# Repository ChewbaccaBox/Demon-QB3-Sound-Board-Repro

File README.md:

# Demon-QB3-Sound-Board

***UNTESTED AND POSSIBLY INCOMPLETE***\
Gerbers not included because of this.

Here is my reproduction sound board of those
used in Rockola's Demon and QB3, both based
on Cinematronics hardware. 
So, these games are both impossible to find,
and therefore the sound boards are too.
Demon uses practically a standard Cinematronics
CPU board, and QB3 is a bit more complicated
to make hardware for, but this sound board
should work for the two games.
(QB3 has more ram, a color converter PCB, the sound roms
 dumped are broken. But Demon should work with less trouble!)

**TESTING STATUS:**

no clue! gotta double check the schematic based on the original.
This is being built on solely the two schematics (the QB3 one 
looks more accurate/complete, so leaning towards that one)

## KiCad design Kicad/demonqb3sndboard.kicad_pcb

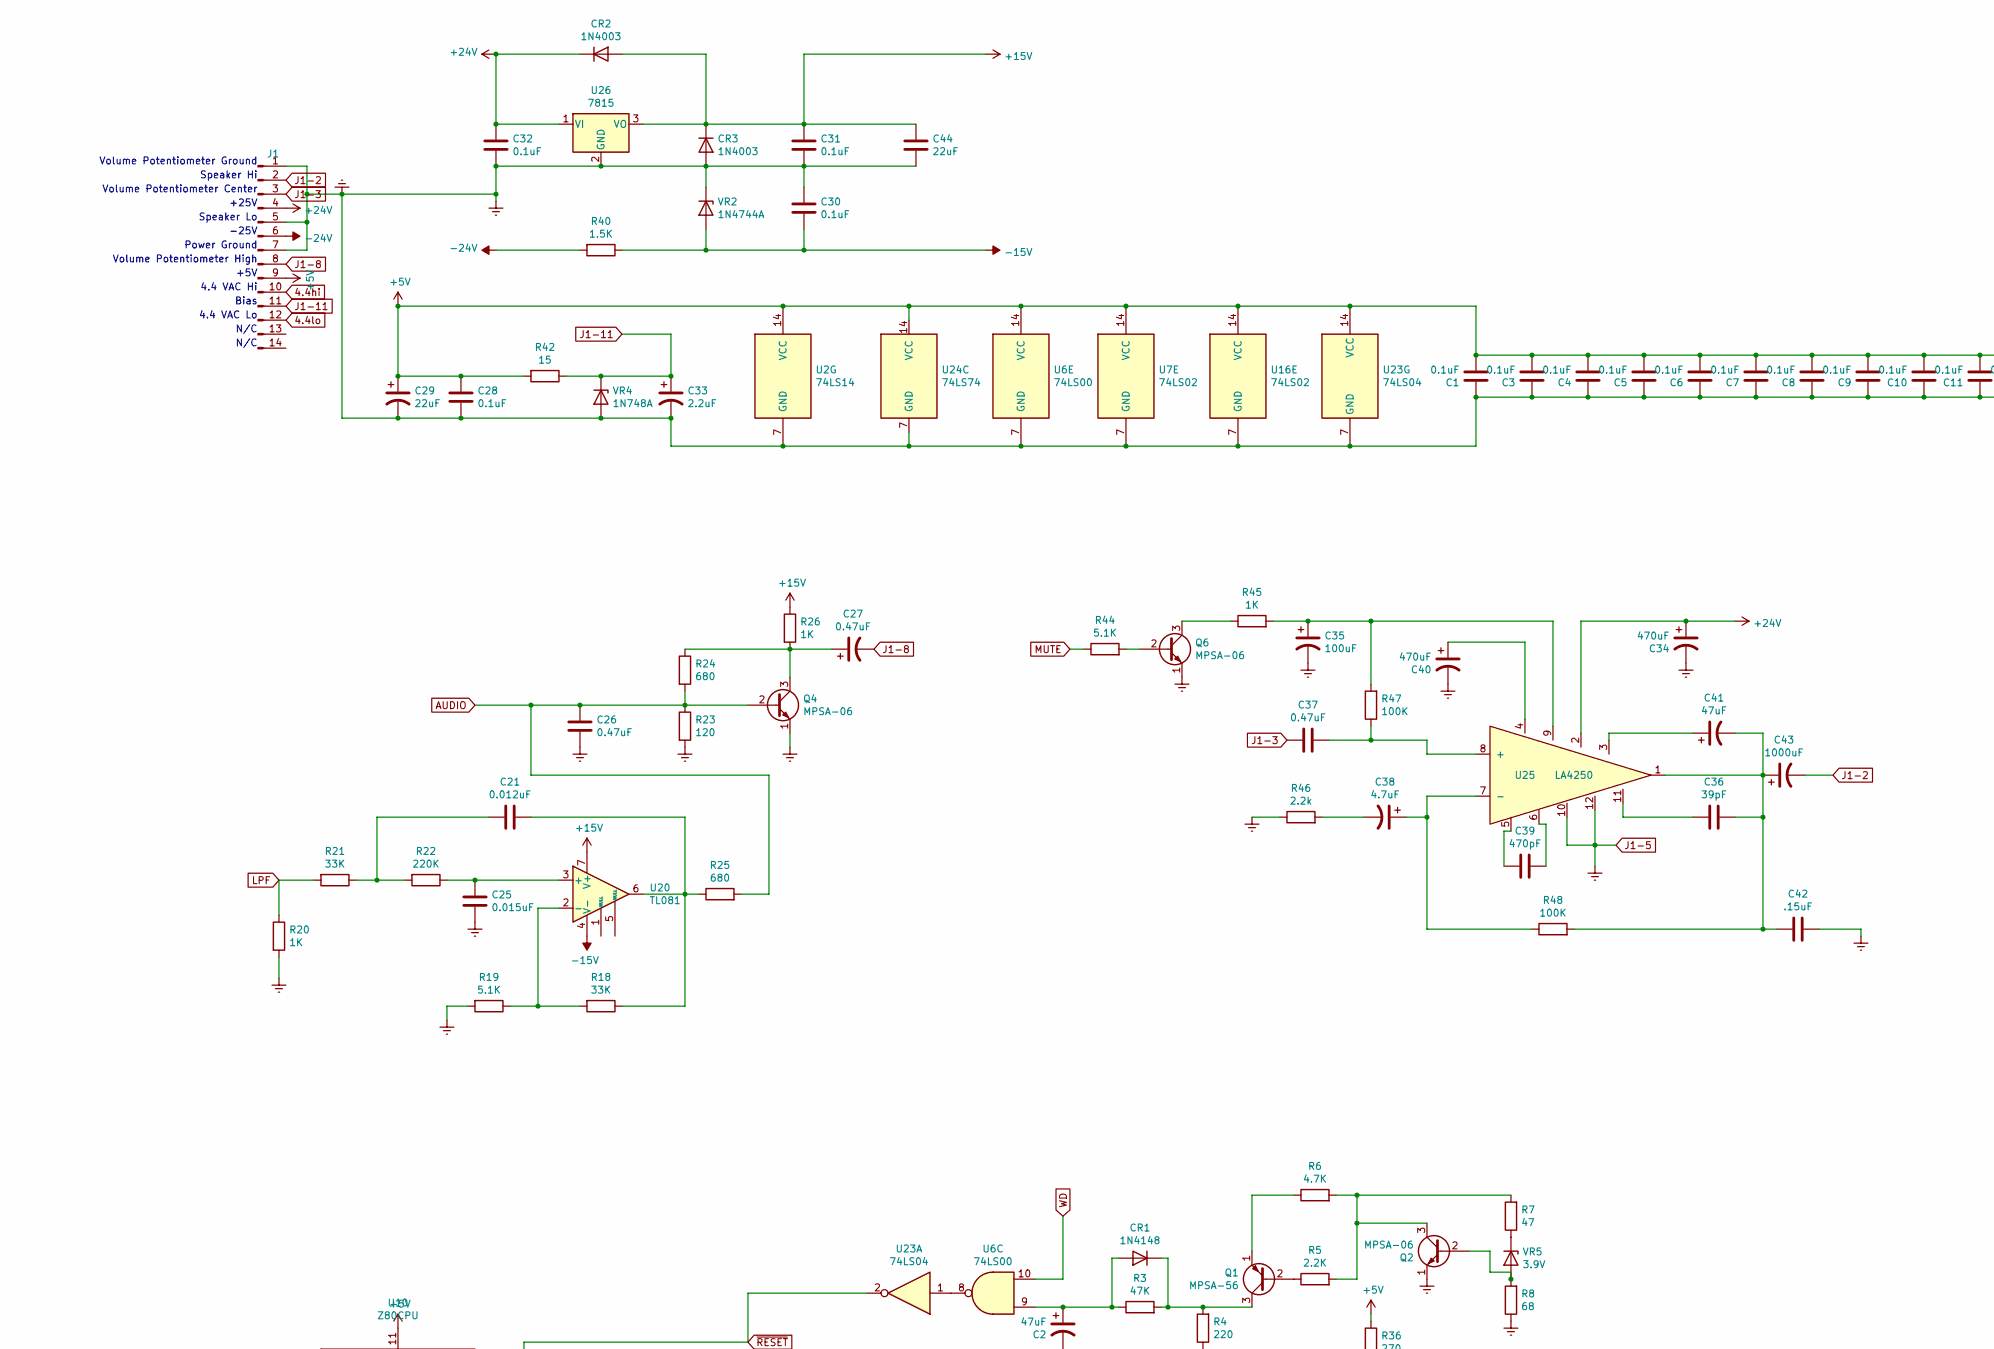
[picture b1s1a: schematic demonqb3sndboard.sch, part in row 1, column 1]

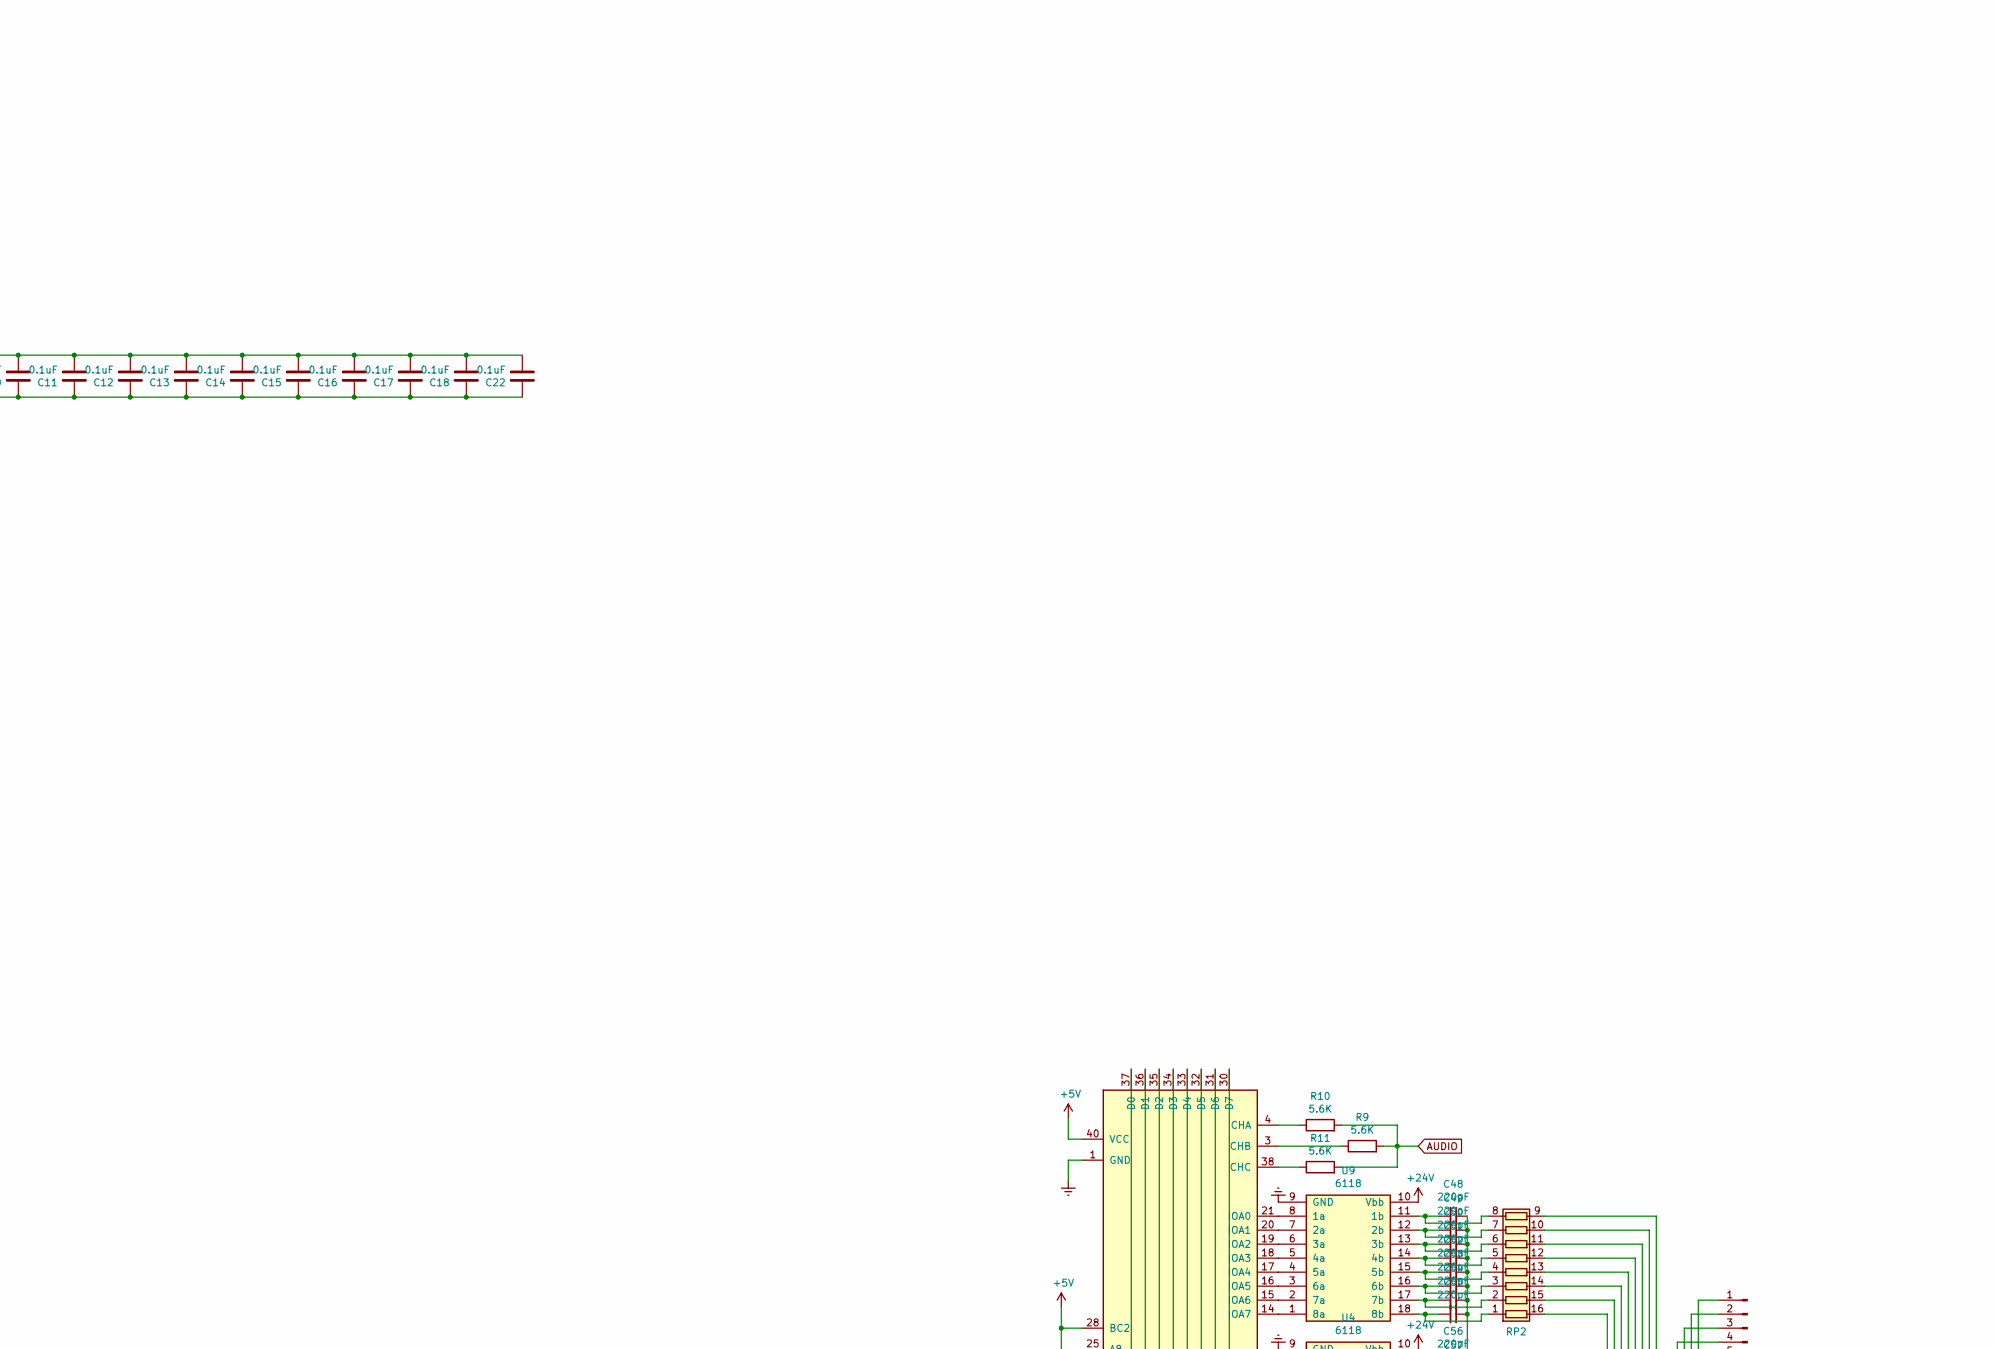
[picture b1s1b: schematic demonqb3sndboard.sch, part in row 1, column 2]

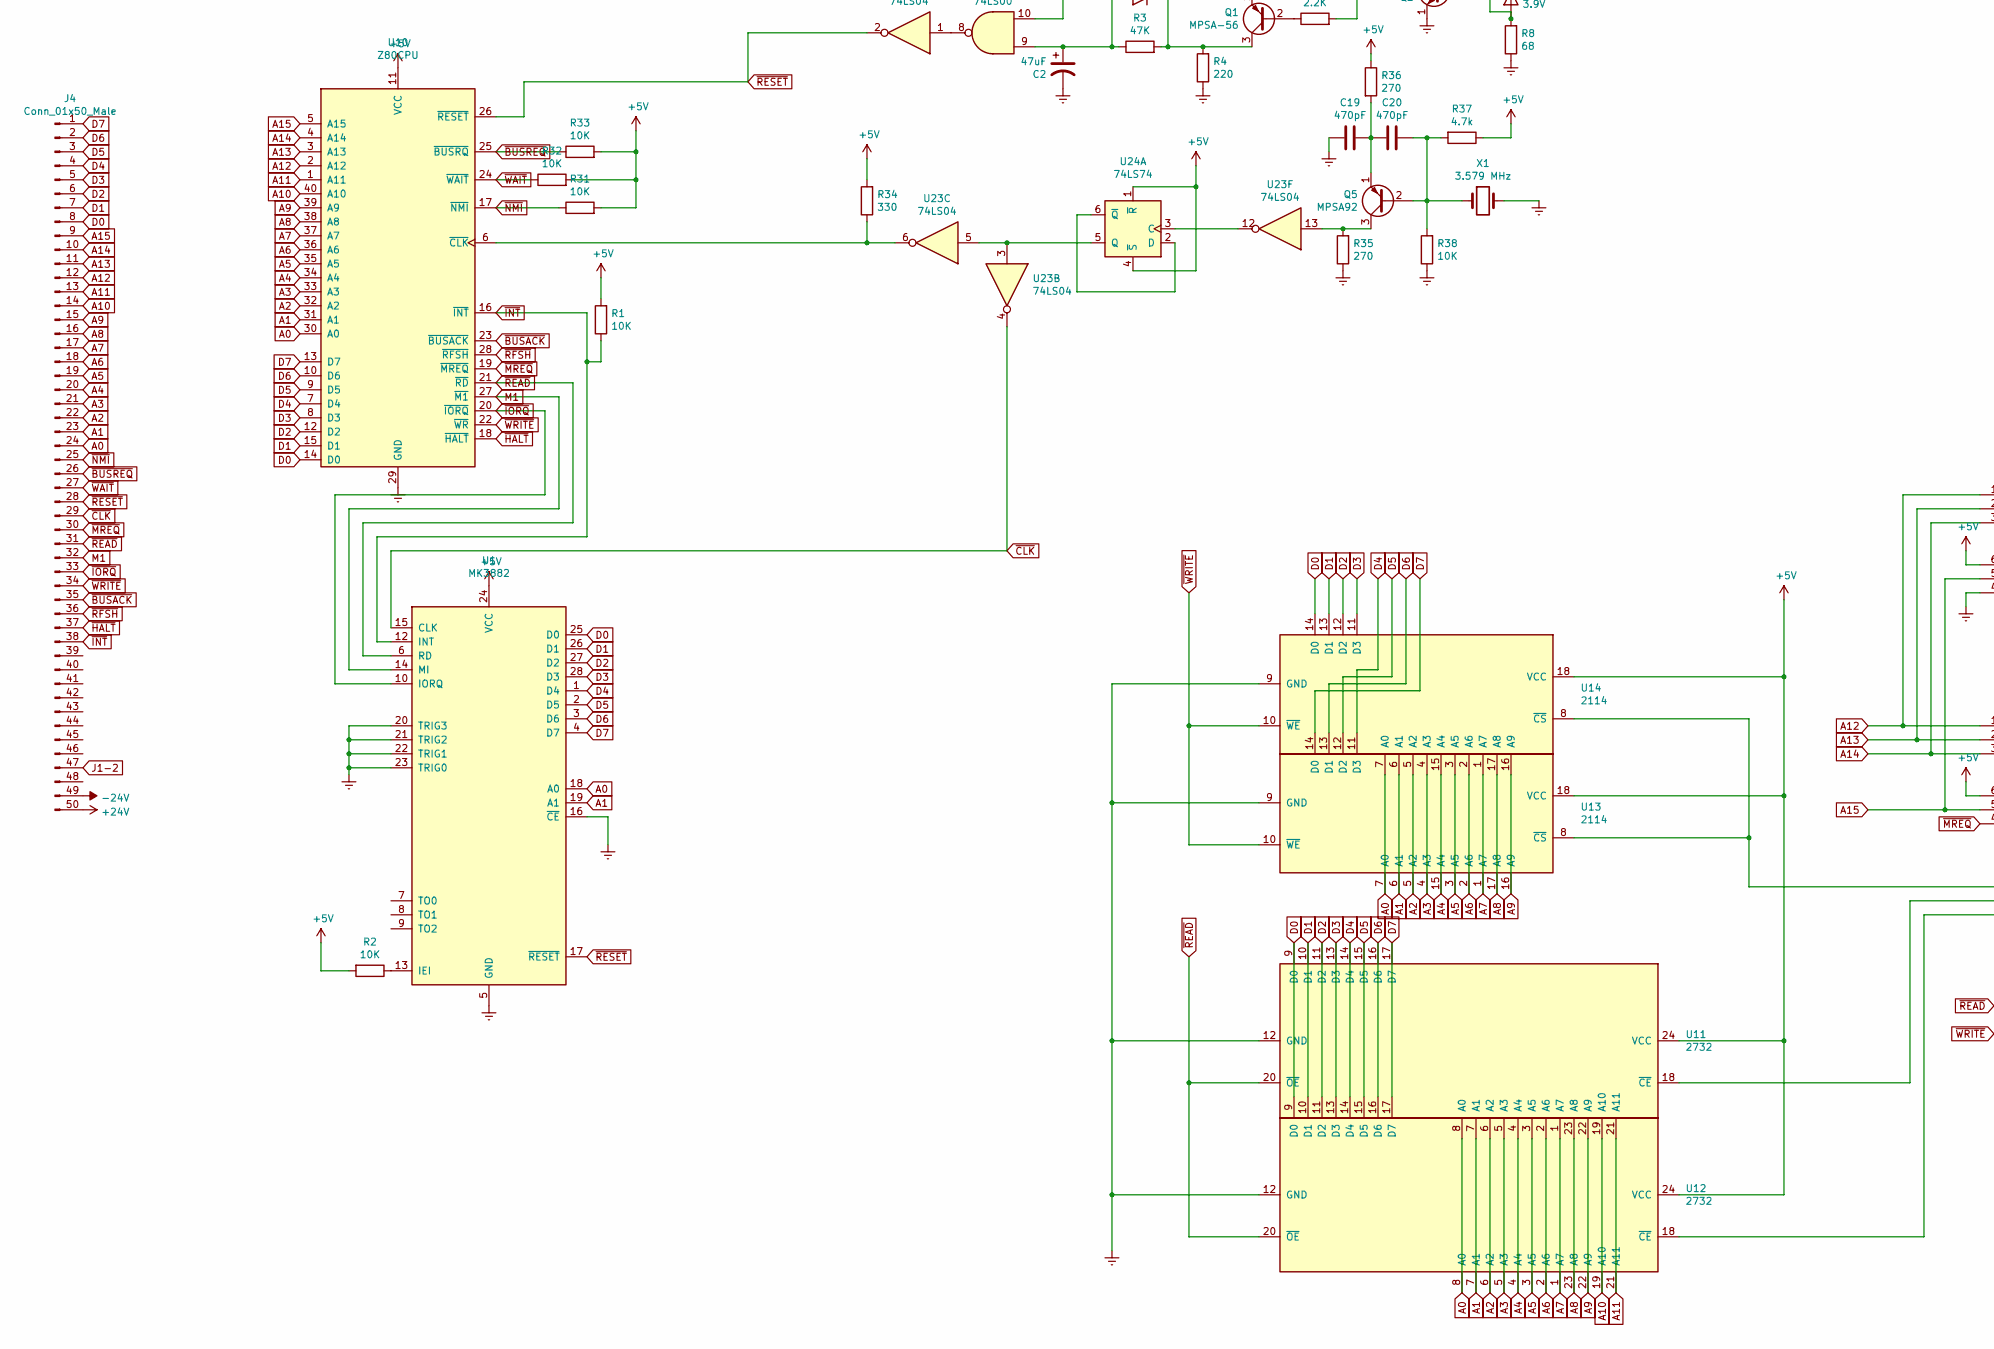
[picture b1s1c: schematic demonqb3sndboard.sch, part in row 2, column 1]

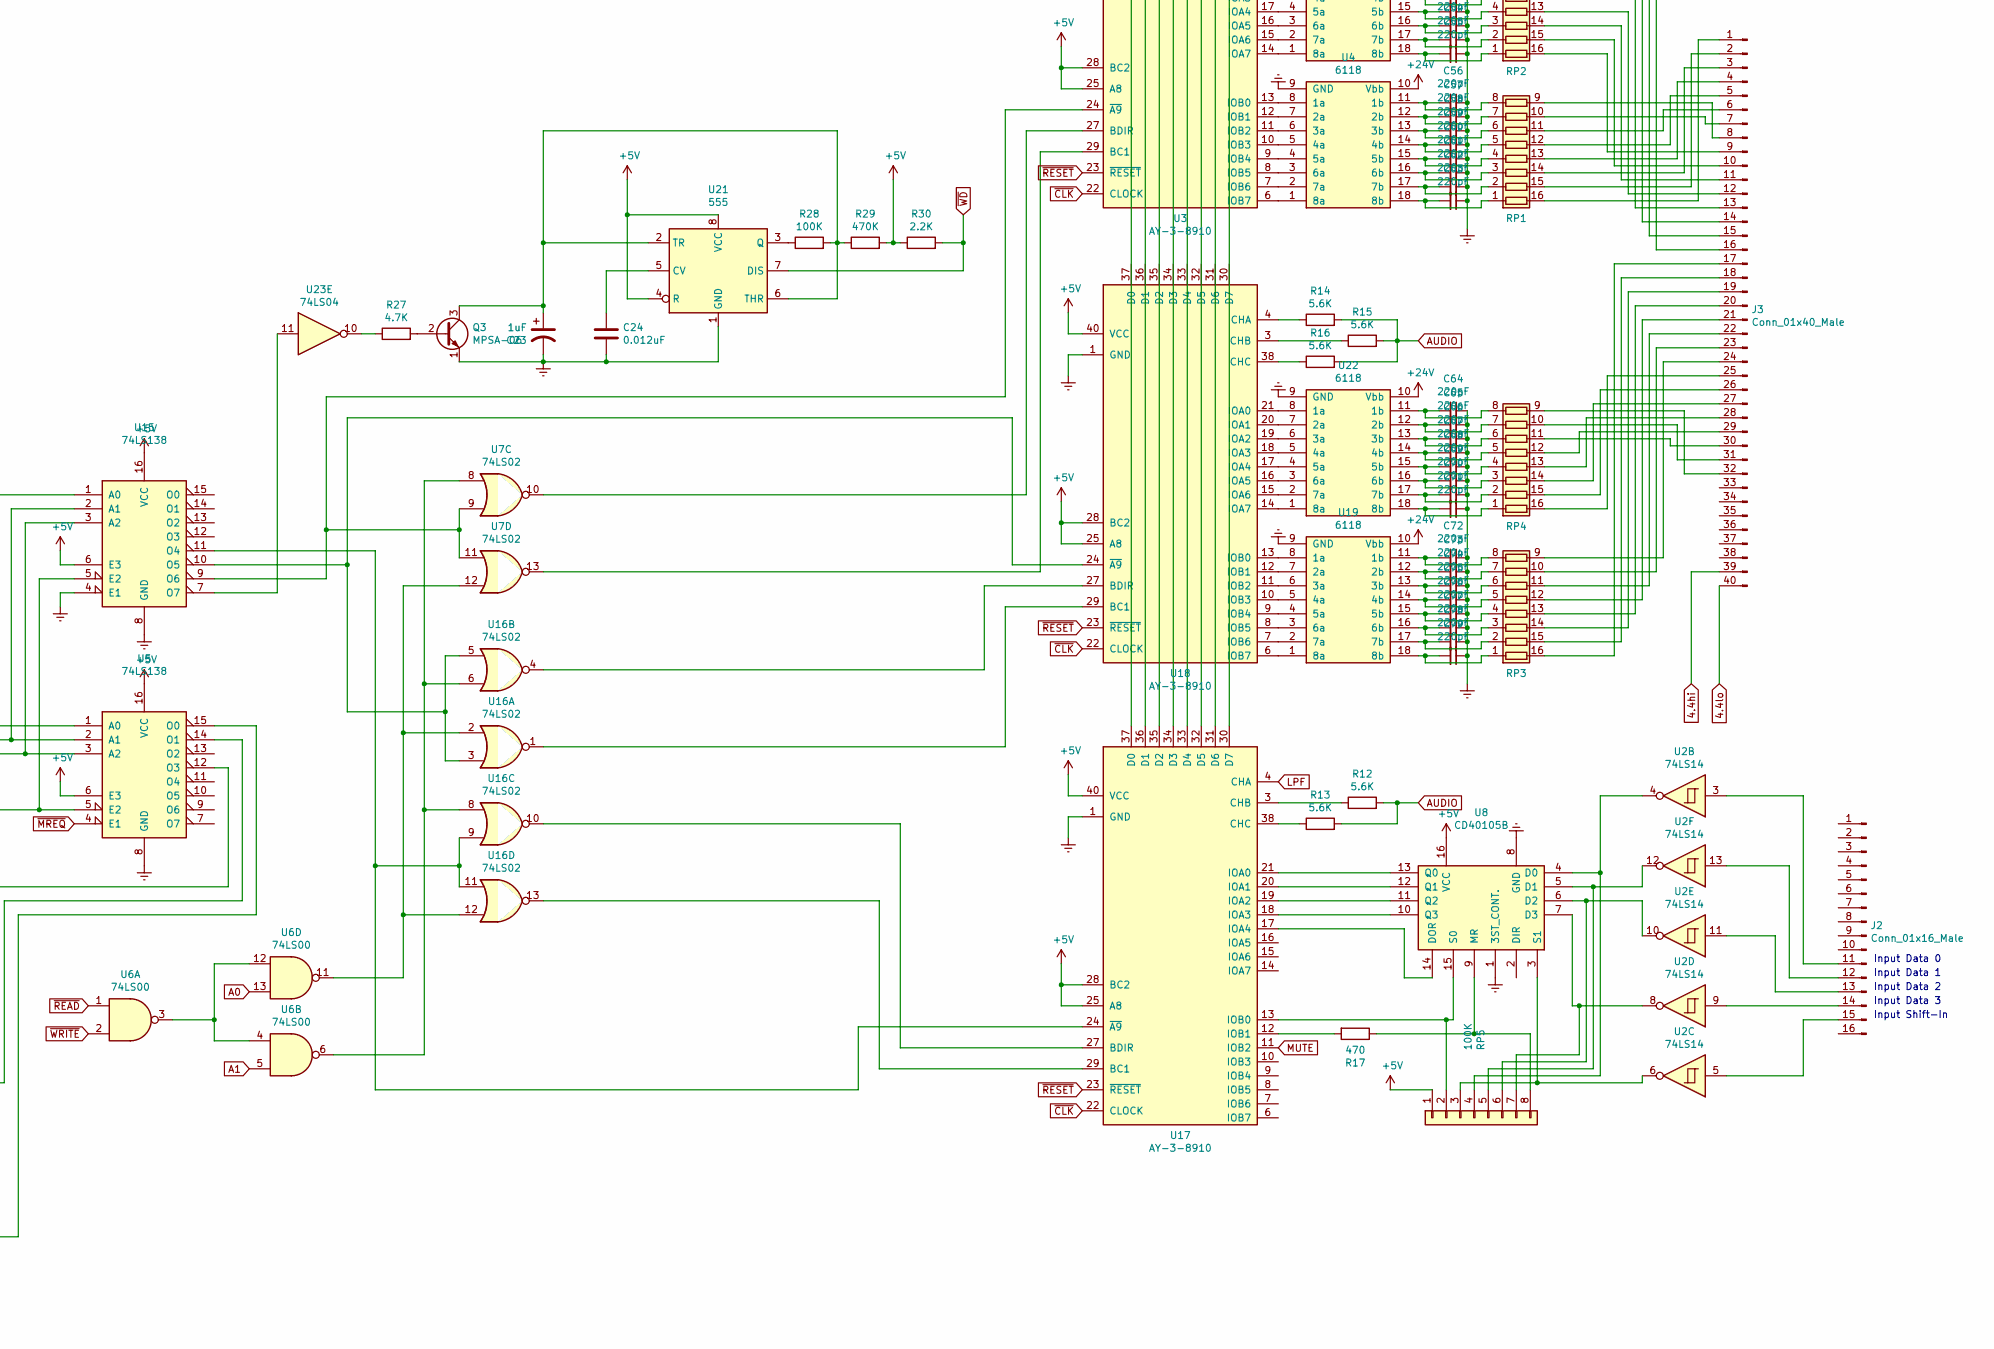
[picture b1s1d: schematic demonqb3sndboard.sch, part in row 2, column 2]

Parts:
C1, C3, C4, C5, C6, C7, C8, C9, C10, C11, C12, C13, C14, C15, C16, C17, C18, C22, C28, C30, C31, C32: 0.1uF; C_Disc_D7.0mm_W2.5mm_P5.00mm
C2: 47uF; CP_Radial_D10.0mm_P5.00mm
C19, C20, C39: 470pF; C_Disc_D7.0mm_W2.5mm_P5.00mm
C21, C24: 0.012uF; C_Disc_D12.5mm_W5.0mm_P10.00mm
C23: 1uF; C_Disc_D10.0mm_W2.5mm_P5.00mm
C25: 0.015uF; C_Disc_D12.5mm_W5.0mm_P10.00mm
C26, C27: 0.47uF; C_Disc_D7.0mm_W2.5mm_P5.00mm
C29, C44: 22uF; C_Disc_D7.0mm_W2.5mm_P5.00mm
C33: 2.2uF; C_Disc_D7.0mm_W2.5mm_P5.00mm
C34, C40: 470uF; CP_Radial_D10.0mm_P5.00mm
C35: 100uF; CP_Radial_D5.0mm_P2.50mm
C36: 39pF; C_Disc_D7.0mm_W2.5mm_P5.00mm
C37: 0.47uF; CP_Radial_D5.0mm_P2.50mm
C38: 4.7uF; C_Disc_D7.0mm_W2.5mm_P5.00mm
C41: 47uF; CP_Radial_D5.0mm_P2.50mm
C42: .15uF; C_Disc_D7.0mm_W2.5mm_P5.00mm
C43: 1000uF; CP_Axial_L30.0mm_D10.0mm_P35.00mm_Horizontal
C48, C49, C50, C51, C52, C53, C54, C55, C56, C57, C58, C59, C60, C61, C62, C63, C64, C65, C66, C67, C68, C69, C70, C71, C72, C73, C74, C75, C76, C77, C78, C79: 220pF; C_Disc_D7.0mm_W2.5mm_P5.00mm
CR1: 1N4148; D_DO-41_SOD81_P10.16mm_Horizontal
CR2, CR3: 1N4003; D_DO-41_SOD81_P10.16mm_Horizontal
J1: Conn_01x14_Male; PinHeader_01x14_0.156
J2: Conn_01x16_Male; PinHeader_2x08_P2.54mm_Vertical
J3: Conn_01x40_Male; 40pinEdgeConnector2.54mm
J4: Conn_01x50_Male; 50pinEdgeConnector2.54mm
Q1: MPSA-56; TO-92_Inline
Q2, Q3, Q4, Q6: MPSA-06; TO-92_Inline
Q5: MPSA92; TO-92_Inline
R1, R2, R31, R32, R33, R38: 10K; R_Axial_DIN0309_L9.0mm_D3.2mm_P12.70mm_Horizontal
R3: 47K; R_Axial_DIN0309_L9.0mm_D3.2mm_P12.70mm_Horizontal
R4: 220; R_Axial_DIN0309_L9.0mm_D3.2mm_P12.70mm_Horizontal
R5, R30: 2.2K; R_Axial_DIN0309_L9.0mm_D3.2mm_P12.70mm_Horizontal
R6, R27: 4.7K; R_Axial_DIN0309_L9.0mm_D3.2mm_P12.70mm_Horizontal
R7: 47; R_Axial_DIN0309_L9.0mm_D3.2mm_P12.70mm_Horizontal
R8: 68; R_Axial_DIN0309_L9.0mm_D3.2mm_P12.70mm_Horizontal
R9, R10, R11, R12, R13, R14, R15, R16: 5.6K; R_Axial_DIN0309_L9.0mm_D3.2mm_P12.70mm_Horizontal
R17: 470; R_Axial_DIN0309_L9.0mm_D3.2mm_P12.70mm_Horizontal
R18, R21: 33K; R_Axial_DIN0309_L9.0mm_D3.2mm_P12.70mm_Horizontal
R19, R44: 5.1K; R_Axial_DIN0309_L9.0mm_D3.2mm_P12.70mm_Horizontal
R20, R26, R45: 1K; R_Axial_DIN0309_L9.0mm_D3.2mm_P12.70mm_Horizontal
R22: 220K; R_Axial_DIN0309_L9.0mm_D3.2mm_P12.70mm_Horizontal
R23: 120; R_Axial_DIN0309_L9.0mm_D3.2mm_P12.70mm_Horizontal
R24, R25: 680; R_Axial_DIN0309_L9.0mm_D3.2mm_P12.70mm_Horizontal
R28, R47, R48: 100K; R_Axial_DIN0309_L9.0mm_D3.2mm_P12.70mm_Horizontal
R29: 470K; R_Axial_DIN0309_L9.0mm_D3.2mm_P12.70mm_Horizontal
R34: 330; R_Axial_DIN0309_L9.0mm_D3.2mm_P12.70mm_Horizontal
R35, R36: 270; R_Axial_DIN0309_L9.0mm_D3.2mm_P12.70mm_Horizontal
R37: 4.7k; R_Axial_DIN0309_L9.0mm_D3.2mm_P12.70mm_Horizontal
R40: 1.5K; R_Axial_DIN0309_L9.0mm_D3.2mm_P12.70mm_Horizontal
R42: 15; R_Axial_DIN0309_L9.0mm_D3.2mm_P12.70mm_Horizontal
R46: 2.2k; R_Axial_DIN0309_L9.0mm_D3.2mm_P12.70mm_Horizontal
RP1, RP2, RP3, RP4: R_Pack08; DIP-16_W7.62mm_LongPads
RP5: 100K; PinHeader_1x08_P2.54mm_Vertical
U1: MK3882; DIP-28_W15.24mm_LongPads
U2: 74LS14; DIP-14_W7.62mm_LongPads
U3, U17, U18: AY-3-8910; DIP-40_W15.24mm_LongPads
U4, U9, U19, U22: 6118; DIP-18_W7.62mm_LongPads
U5, U15: 74LS138; DIP-16_W7.62mm_LongPads
U6: 74LS00; DIP-14_W7.62mm_LongPads
U7, U16: 74LS02; DIP-14_W7.62mm_LongPads
U8: CD40105B; DIP-16_W7.62mm_LongPads
U10: Z80CPU; DIP-40_W15.24mm_LongPads
U11, U12: 2732; DIP-24_W15.24mm_LongPads
U13, U14: 2114; DIP-18_W7.62mm_LongPads
U20: TL081; DIP-8_W7.62mm_LongPads
U21: 555; DIP-8_W7.62mm_LongPads
U23: 74LS04; DIP-14_W7.62mm_LongPads
U24: 74LS74; DIP-14_W7.62mm_LongPads
U25: LA4250; PinSocket_1x12_P2.54mm_Vertical
U26: 7815; TO-220-3_Vertical
VR2: 1N4744A; D_DO-41_SOD81_P10.16mm_Horizontal
VR4: 1N748A; D_DO-41_SOD81_P10.16mm_Horizontal
VR5: 3.9V; D_DO-41_SOD81_P10.16mm_Horizontal
X1: 3.579 MHz; Crystal_HC18-U_Vertical

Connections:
4.4hi: J1.10, J3.39
4.4lo: J1.12, J3.40
+5V: C1.2, C3.2, C4.2, C5.2, C6.2, C7.2, C8.2, C9.2, C10.2, C11.2, C12.2, C13.2, C14.2, C15.2, C16.2, C17.2, C18.2, C22.2, C28.1, C29.1, J1.9, R1.2, R2.2, R29.2, R30.1, R31.2, R32.2, R33.2, R34.2, R36.1, R37.1, R42.2, RP5.1, U1.24 (VCC), U2.14 (VCC), U3.25 (A8), U3.28 (BC2), U3.40 (VCC), U5.6 (E3), U5.16 (VCC), U6.14 (VCC), U7.14 (VCC), U8.16 (VCC), U10.11 (VCC), U11.24 (VCC), U12.24 (VCC), U13.18 (VCC), U14.18 (VCC), U15.6 (E3), U15.16 (VCC), U16.14 (VCC), U17.25 (A8), U17.28 (BC2), U17.40 (VCC), U18.25 (A8), U18.28 (BC2), U18.40 (VCC), U21.4 (R), U21.8 (VCC), U23.14 (VCC), U24.1 (~R), U24.4 (~S), U24.14 (VCC)
+15V: C31.1, C44.1, CR2.2 (A), CR3.1 (K), R26.1, U20.7 (V+), U26.3 (VO)
+24V: C32.1, C34.1, CR2.1 (K), J1.4, J4.50, U4.10 (Vbb), U9.10 (Vbb), U19.10 (Vbb), U22.10 (Vbb), U25.2, U26.1 (VI)
-15V: C30.2, R40.1, U20.4 (V-), VR2.2 (A)
-24V: J1.6, J4.49, R40.2
A0: J4.24, U1.18 (A0), U6.13, U10.30 (A0), U11.8 (A0), U12.8 (A0), U13.7 (A0), U14.7 (A0)
A1: J4.23, U1.19 (A1), U6.5, U10.31 (A1), U11.7 (A1), U12.7 (A1), U13.6 (A1), U14.6 (A1)
A2: J4.22, U10.32 (A2), U11.6 (A2), U12.6 (A2), U13.5 (A2), U14.5 (A2)
A3: J4.21, U10.33 (A3), U11.5 (A3), U12.5 (A3), U13.4 (A3), U14.4 (A3)
A4: J4.20, U10.34 (A4), U11.4 (A4), U12.4 (A4), U13.15 (A4), U14.15 (A4)
A5: J4.19, U10.35 (A5), U11.3 (A5), U12.3 (A5), U13.3 (A5), U14.3 (A5)
A6: J4.18, U10.36 (A6), U11.2 (A6), U12.2 (A6), U13.2 (A6), U14.2 (A6)
A7: J4.17, U10.37 (A7), U11.1 (A7), U12.1 (A7), U13.1 (A7), U14.1 (A7)
A8: J4.16, U10.38 (A8), U11.23 (A8), U12.23 (A8), U13.17 (A8), U14.17 (A8)
A9: J4.15, U10.39 (A9), U11.22 (A9), U12.22 (A9), U13.16 (A9), U14.16 (A9)
A10: J4.14, U10.40 (A10), U11.19 (A10), U12.19 (A10)
A11: J4.13, U10.1 (A11), U11.21 (A11), U12.21 (A11)
A12: J4.12, U5.1 (A0), U10.2 (A12), U15.1 (A0)
A13: J4.11, U5.2 (A1), U10.3 (A13), U15.2 (A1)
A14: J4.10, U5.3 (A2), U10.4 (A14), U15.3 (A2)
A15: J4.9, U5.5 (E2), U10.5 (A15), U15.5 (E2)
AUDIO: C26.2, Q4.2 (B), R9.2, R10.2, R11.2, R12.2, R13.2, R14.2, R15.2, R16.2, R23.1, R24.2, R25.2
D0: J4.8, U1.25 (D0), U10.14 (D0), U11.9 (D0), U12.9 (D0), U14.14 (D0)
D1: J4.7, U1.26 (D1), U10.15 (D1), U11.10 (D1), U12.10 (D1), U14.13 (D1)
D2: J4.6, U1.27 (D2), U10.12 (D2), U11.11 (D2), U12.11 (D2), U14.12 (D2)
D3: J4.5, U1.28 (D3), U10.8 (D3), U11.13 (D3), U12.13 (D3), U14.11 (D3)
D4: J4.4, U1.1 (D4), U10.7 (D4), U11.14 (D4), U12.14 (D4), U13.11 (D3)
D5: J4.3, U1.2 (D5), U10.9 (D5), U11.15 (D5), U12.15 (D5), U13.12 (D2)
D6: J4.2, U1.3 (D6), U10.10 (D6), U11.16 (D6), U12.16 (D6), U13.13 (D1)
D7: J4.1, U1.4 (D7), U10.13 (D7), U11.17 (D7), U12.17 (D7), U13.14 (D0)
J1-2: C43.2, J1.2, J4.47
J1-3: C37.1, J1.3
J1-5: C1.1, C2.2, C3.1, C4.1, C5.1, C6.1, C7.1, C8.1, C9.1, C10.1, C11.1, C12.1, C13.1, C14.1, C15.1, C16.1, C17.1, C18.1, C19.2, C22.1, C23.2, C24.1, C25.2, C26.1, C28.2, C29.2, C30.1, C31.2, C32.2, C33.2, C34.2, C35.2, C40.2, C42.2, C44.2, C48.1, C49.1, C50.1, C51.1, C52.1, C53.1, C54.1, C55.1, C56.1, C57.1, C58.1, C59.1, C60.1, C61.1, C62.1, C63.1, C64.1, C65.1, C66.1, C67.1, C68.1, C69.1, C70.1, C71.1, C72.1, C73.1, C74.1, C75.1, C76.1, C77.1, C78.1, C79.1, CR3.2 (A), J1.1, J1.5, J1.7, Q2.1 (E), Q3.1 (E), Q4.1 (E), Q6.1 (E), R4.1, R8.1, R19.2, R20.2, R23.2, R35.1, R38.1, R46.1, U1.5 (GND), U1.16 (~CE~), U1.20 (TRIG3), U1.21 (TRIG2), U1.22 (TRIG1), U1.23 (TRIG0), U2.7 (GND), U3.1 (GND), U4.9 (GND), U5.8 (GND), U6.7 (GND), U7.7 (GND), U8.1 (3ST_CONT.), U8.8 (GND), U9.9 (GND), U10.29 (GND), U11.12 (GND), U12.12 (GND), U13.9 (GND), U14.9 (GND), U15.4 (E1), U15.8 (GND), U16.7 (GND), U17.1 (GND), U18.1 (GND), U19.9 (GND), U21.1 (GND), U22.9 (GND), U23.7 (GND), U24.7 (GND), U25.10, U25.12, U26.2 (GND), VR2.1 (K), VR4.2 (A), X1.2
J1-8: C27.2, J1.8
J1-11: C33.1, J1.11, R42.1, VR4.1 (K)
LPF: R20.1, R21.2, U17.4 (CHA)
M1: J4.32, U1.14 (MI), U10.27 (~M1~)
MUTE: R44.1, U17.11 (IOB2)
unnamed: C2.1, CR1.2 (A), R3.1, U6.9
unnamed: C19.1, C20.2, Q5.1 (E), R36.2
unnamed: C20.1, Q5.2 (B), R37.2, R38.2, X1.1
unnamed: C21.1, R21.1, R22.2
unnamed: C21.2, R18.1, R25.1, U20.6
unnamed: C23.1, Q3.3 (C), R28.2, R29.1, U21.2 (TR), U21.6 (THR)
unnamed: C24.2, U21.5 (CV)
unnamed: C25.1, R22.1, U20.3 (+)
unnamed: C27.1, Q4.3 (C), R24.1, R26.2
unnamed: C35.1, R45.2, R47.2, U25.9
unnamed: C36.1, U25.11
unnamed: C36.2, C41.2, C42.1, C43.1, R48.2, U25.1
unnamed: C37.2, R47.1, U25.8 (+)
unnamed: C38.1, R48.1, U25.7 (-)
unnamed: C38.2, R46.2
unnamed: C39.1, U25.5
unnamed: C39.2, U25.6
unnamed: C40.1, U25.4
unnamed: C41.1, U25.3
unnamed: C48.2, RP2.8 (R8.1), U9.11 (1b)
unnamed: C49.2, RP2.7 (R7.1), U9.12 (2b)
unnamed: C50.2, RP2.6 (R6.1), U9.13 (3b)
unnamed: C51.2, RP2.5 (R5.1), U9.14 (4b)
unnamed: C52.2, RP2.4 (R4.1), U9.15 (5b)
unnamed: C53.2, RP2.3 (R3.1), U9.16 (6b)
unnamed: C54.2, RP2.2 (R2.1), U9.17 (7b)
unnamed: C55.2, RP2.1 (R1.1), U9.18 (8b)
unnamed: C56.2, RP1.8 (R8.1), U4.11 (1b)
unnamed: C57.2, RP1.7 (R7.1), U4.12 (2b)
unnamed: C58.2, RP1.6 (R6.1), U4.13 (3b)
unnamed: C59.2, RP1.5 (R5.1), U4.14 (4b)
unnamed: C60.2, RP1.4 (R4.1), U4.15 (5b)
unnamed: C61.2, RP1.3 (R3.1), U4.16 (6b)
unnamed: C62.2, RP1.2 (R2.1), U4.17 (7b)
unnamed: C63.2, RP1.1 (R1.1), U4.18 (8b)
unnamed: C64.2, RP4.8 (R8.1), U22.11 (1b)
unnamed: C65.2, RP4.7 (R7.1), U22.12 (2b)
unnamed: C66.2, RP4.6 (R6.1), U22.13 (3b)
unnamed: C67.2, RP4.5 (R5.1), U22.14 (4b)
unnamed: C68.2, RP4.4 (R4.1), U22.15 (5b)
unnamed: C69.2, RP4.3 (R3.1), U22.16 (6b)
unnamed: C70.2, RP4.2 (R2.1), U22.17 (7b)
unnamed: C71.2, RP4.1 (R1.1), U22.18 (8b)
unnamed: C72.2, RP3.8 (R8.1), U19.11 (1b)
unnamed: C73.2, RP3.7 (R7.1), U19.12 (2b)
unnamed: C74.2, RP3.6 (R6.1), U19.13 (3b)
unnamed: C75.2, RP3.5 (R5.1), U19.14 (4b)
unnamed: C76.2, RP3.4 (R4.1), U19.15 (5b)
unnamed: C77.2, RP3.3 (R3.1), U19.16 (6b)
unnamed: C78.2, RP3.2 (R2.1), U19.17 (7b)
unnamed: C79.2, RP3.1 (R1.1), U19.18 (8b)
unnamed: CR1.1 (K), Q1.3 (C), R3.2, R4.2
unnamed: J2.11, U2.3
unnamed: J2.12, U2.13
unnamed: J2.13, U2.11
unnamed: J2.14, U2.9
unnamed: J2.15, U2.5
unnamed: J3.1, RP1.16 (R1.2)
unnamed: J3.2, RP1.15 (R2.2)
unnamed: J3.3, RP1.14 (R3.2)
unnamed: J3.4, RP1.13 (R4.2)
unnamed: J3.5, RP1.12 (R5.2)
unnamed: J3.6, RP1.11 (R6.2)
unnamed: J3.7, RP1.10 (R7.2)
unnamed: J3.8, RP1.9 (R8.2)
unnamed: J3.9, RP2.16 (R1.2)
unnamed: J3.10, RP2.15 (R2.2)
unnamed: J3.11, RP2.14 (R3.2)
unnamed: J3.12, RP2.13 (R4.2)
unnamed: J3.13, RP2.12 (R5.2)
unnamed: J3.14, RP2.11 (R6.2)
unnamed: J3.15, RP2.10 (R7.2)
unnamed: J3.16, RP2.9 (R8.2)
unnamed: J3.17, RP3.16 (R1.2)
unnamed: J3.18, RP3.15 (R2.2)
unnamed: J3.19, RP3.14 (R3.2)
unnamed: J3.20, RP3.13 (R4.2)
unnamed: J3.21, RP3.12 (R5.2)
unnamed: J3.22, RP3.11 (R6.2)
unnamed: J3.23, RP3.10 (R7.2)
unnamed: J3.24, RP3.9 (R8.2)
unnamed: J3.25, RP4.16 (R1.2)
unnamed: J3.26, RP4.15 (R2.2)
unnamed: J3.27, RP4.14 (R3.2)
unnamed: J3.28, RP4.13 (R4.2)
unnamed: J3.29, RP4.12 (R5.2)
unnamed: J3.30, RP4.11 (R6.2)
unnamed: J3.31, RP4.10 (R7.2)
unnamed: J3.32, RP4.9 (R8.2)
unnamed: Q1.1 (E), R6.1
unnamed: Q1.2 (B), R5.1
unnamed: Q2.2 (B), R8.2, VR5.2 (A)
unnamed: Q2.3 (C), R5.2, R6.2, R7.2
unnamed: Q3.2 (B), R27.2
unnamed: Q5.3 (C), R35.2, U23.13
unnamed: Q6.2 (B), R44.2
unnamed: Q6.3 (C), R45.1
unnamed: R2.1, U1.13 (IEI)
unnamed: R7.1, VR5.1 (K)
unnamed: R9.1, U3.3 (CHB)
unnamed: R10.1, U3.4 (CHA)
unnamed: R11.1, U3.38 (CHC)
unnamed: R12.1, U17.3 (CHB)
unnamed: R13.1, U17.38 (CHC)
unnamed: R14.1, U18.4 (CHA)
unnamed: R15.1, U18.3 (CHB)
unnamed: R16.1, U18.38 (CHC)
unnamed: R17.1, RP5.8, U8.9 (MR)
unnamed: R17.2, U17.12 (IOB1)
unnamed: R18.2, R19.1, U20.2 (-)
unnamed: R27.1, U23.10
unnamed: R28.1, U21.3 (Q)
unnamed: R34.1, U10.6 (~CLK~), U23.6
unnamed: RP5.2, U8.15 (S0), U17.13 (IOB0)
unnamed: RP5.3, U2.6, U8.3 (S1)
unnamed: RP5.4, U2.4, U8.4 (D0)
unnamed: RP5.5, U2.12, U8.5 (D1)
unnamed: RP5.6, U2.10, U8.6 (D2)
unnamed: RP5.7, U2.8, U8.7 (D3)
unnamed: U3.6 (IOB7), U4.1 (8a)
unnamed: U3.7 (IOB6), U4.2 (7a)
unnamed: U3.8 (IOB5), U4.3 (6a)
unnamed: U3.9 (IOB4), U4.4 (5a)
unnamed: U3.10 (IOB3), U4.5 (4a)
unnamed: U3.11 (IOB2), U4.6 (3a)
unnamed: U3.12 (IOB1), U4.7 (2a)
unnamed: U3.13 (IOB0), U4.8 (1a)
unnamed: U3.14 (IOA7), U9.1 (8a)
unnamed: U3.15 (IOA6), U9.2 (7a)
unnamed: U3.16 (IOA5), U9.3 (6a)
unnamed: U3.17 (IOA4), U9.4 (5a)
unnamed: U3.18 (IOA3), U9.5 (4a)
unnamed: U3.19 (IOA2), U9.6 (3a)
unnamed: U3.20 (IOA1), U9.7 (2a)
unnamed: U3.21 (IOA0), U9.8 (1a)
unnamed: U3.27 (BDIR), U7.10
unnamed: U3.29 (BC1), U7.13
unnamed: U6.3, U6.4, U6.12
unnamed: U5.14 (O1), U11.18 (~CE~)
unnamed: U5.15 (O0), U12.18 (~CE~)
unnamed: U5.12 (O3), U13.8 (~CS~), U14.8 (~CS~)
unnamed: U15.7 (O7), U23.11
unnamed: U3.24 (~A9~), U7.9, U7.11, U15.9 (O6)
unnamed: U15.10 (O5), U16.3, U16.5, U18.24 (~A9~)
unnamed: U15.11 (O4), U16.9, U16.11, U17.24 (~A9~)
unnamed: U16.1, U18.29 (BC1)
unnamed: U16.4, U18.27 (BDIR)
unnamed: U6.6, U7.8, U16.6, U16.8
unnamed: U16.10, U17.27 (BDIR)
unnamed: U6.11, U7.12, U16.2, U16.12
unnamed: U16.13, U17.29 (BC1)
unnamed: U8.14 (DOR), U17.17 (IOA4)
unnamed: U8.10 (Q3), U17.18 (IOA3)
unnamed: U8.11 (Q2), U17.19 (IOA2)
unnamed: U8.12 (Q1), U17.20 (IOA1)
unnamed: U8.13 (Q0), U17.21 (IOA0)
unnamed: U3.30 (D7), U17.30 (D7)
unnamed: U3.31 (D6), U17.31 (D6)
unnamed: U3.32 (D5), U17.32 (D5)
unnamed: U3.33 (D4), U17.33 (D4)
unnamed: U3.34 (D3), U17.34 (D3)
unnamed: U3.35 (D2), U17.35 (D2)
unnamed: U3.36 (D1), U17.36 (D1)
unnamed: U3.37 (D0), U17.37 (D0)
unnamed: U18.6 (IOB7), U19.1 (8a)
unnamed: U18.7 (IOB6), U19.2 (7a)
unnamed: U18.8 (IOB5), U19.3 (6a)
unnamed: U18.9 (IOB4), U19.4 (5a)
unnamed: U18.10 (IOB3), U19.5 (4a)
unnamed: U18.11 (IOB2), U19.6 (3a)
unnamed: U18.12 (IOB1), U19.7 (2a)
unnamed: U18.13 (IOB0), U19.8 (1a)
unnamed: U18.14 (IOA7), U22.1 (8a)
unnamed: U18.15 (IOA6), U22.2 (7a)
unnamed: U18.16 (IOA5), U22.3 (6a)
unnamed: U18.17 (IOA4), U22.4 (5a)
unnamed: U18.18 (IOA3), U22.5 (4a)
unnamed: U18.19 (IOA2), U22.6 (3a)
unnamed: U18.20 (IOA1), U22.7 (2a)
unnamed: U18.21 (IOA0), U22.8 (1a)
unnamed: U6.8, U23.1
unnamed: U23.3, U23.5, U24.5 (Q)
unnamed: U23.12, U24.3 (C)
unnamed: U24.2 (D), U24.6 (~Q)
WD: U6.10
~BUSACK~: J4.35, U10.23 (~BUSACK~)
~BUSREQ~: J4.26, R33.1, U10.25 (~BUSRQ~)
~CLK~: J4.29, U1.15 (CLK), U3.22 (CLOCK), U17.22 (CLOCK), U18.22 (CLOCK), U23.4
~HALT~: J4.37, U10.18 (~HALT~)
~INT~: J4.38, R1.1, U1.12 (INT), U10.16 (~INT~)
~IORQ~: J4.33, U1.10 (IORQ), U10.20 (~IORQ~)
~MREQ~: J4.30, U5.4 (E1), U10.19 (~MREQ~)
~NMI~: J4.25, R31.1, U10.17 (~NMI~)
~READ~: J4.31, U1.6 (RD), U6.1, U10.21 (~RD~), U11.20 (~OE~), U12.20 (~OE~)
~RESET~: J4.28, U1.17 (~RESET~), U3.23 (~RESET~), U10.26 (~RESET~), U17.23 (~RESET~), U18.23 (~RESET~), U23.2
~RFSH~: J4.36, U10.28 (~RFSH~)
~WAIT~: J4.27, R32.1, U10.24 (~WAIT~)
~WD~: R30.2, U21.7 (DIS)
~WRITE~: J4.34, U6.2, U10.22 (~WR~), U13.10 (~WE~), U14.10 (~WE~)

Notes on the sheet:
Volume Potentiometer Ground
Speaker Hi
Volume Potentiometer Center
+25V
Speaker Lo
-25V
Power Ground
Volume Potentiometer High
+5V
4.4 VAC Hi
4.4 VAC Lo
Bias
N/C
Input Shift-In
Input Data 3
Input Data 2
Input Data 1
Input Data 0
